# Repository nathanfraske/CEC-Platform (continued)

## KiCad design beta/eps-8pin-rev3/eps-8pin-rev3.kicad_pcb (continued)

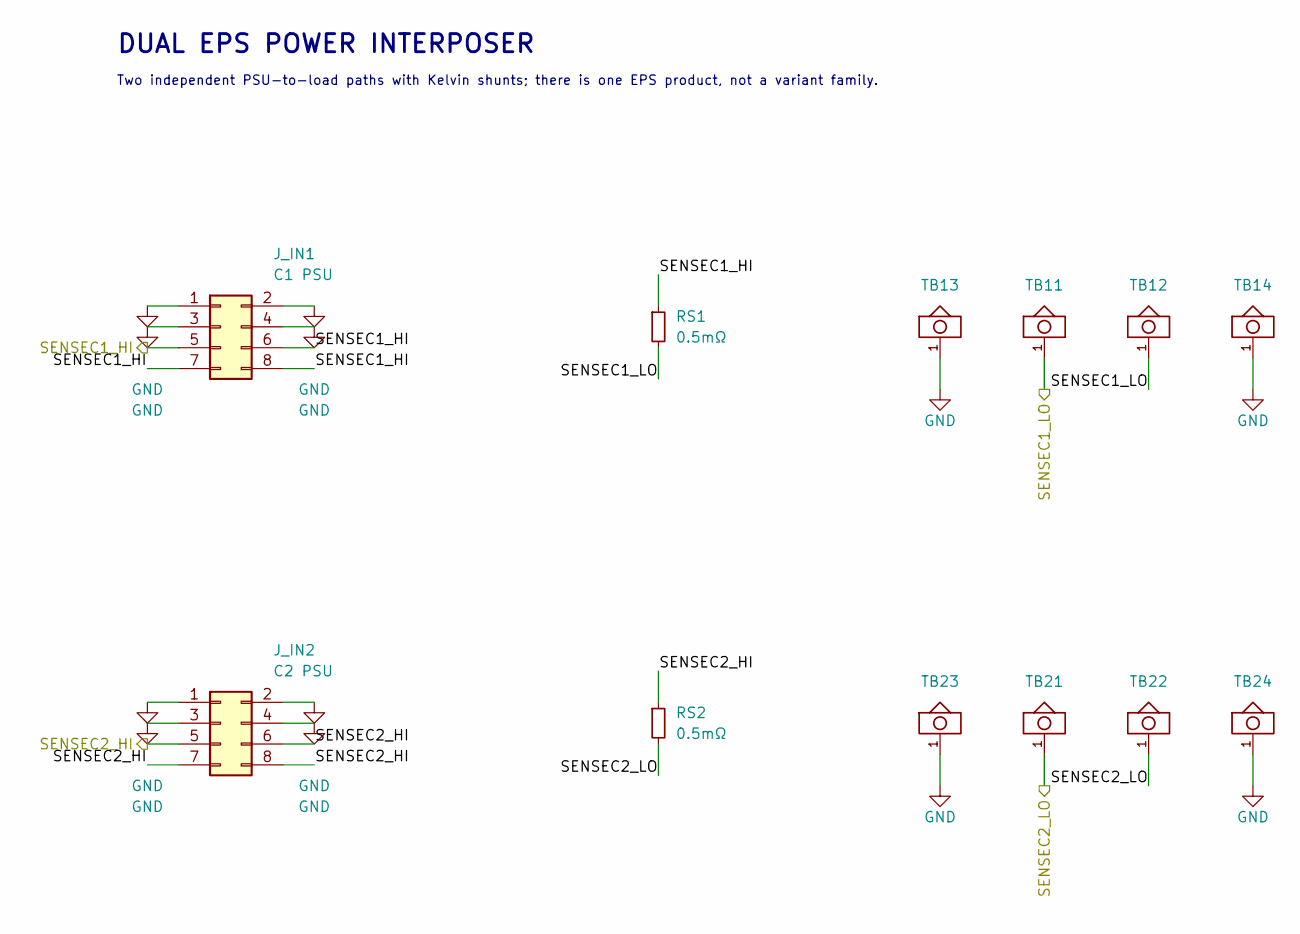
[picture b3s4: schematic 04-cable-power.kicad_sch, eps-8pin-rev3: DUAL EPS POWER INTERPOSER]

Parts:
J_IN1: C1 PSU; Molex_Mini-Fit_Jr_87427-0802_2x04_P4.20mm_RA; MPN 87427-0802
J_IN2: C2 PSU; Molex_Mini-Fit_Jr_87427-0802_2x04_P4.20mm_RA; MPN 87427-0802
RS1, RS2: 0.5mΩ; R_2512_6332Metric; MPN CSS2H-2512R-L500F
TB11, TB12, TB13, TB14, TB21, TB22, TB23, TB24: XFCN T34069; XFCN_T34069_THT_M3_40A; Current Rating 40 A manufacturer-stated; qualification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; MPN T34069; LCSC C481452

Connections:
/SENSEC1_HI: J_IN1.5, J_IN1.6, J_IN1.7, J_IN1.8, RS1.1; also elsewhere on the board
/SENSEC1_LO: RS1.2, TB11.1, TB12.1; also elsewhere on the board
/SENSEC2_HI: J_IN2.5, J_IN2.6, J_IN2.7, J_IN2.8, RS2.1; also elsewhere on the board
/SENSEC2_LO: RS2.2, TB21.1, TB22.1; also elsewhere on the board

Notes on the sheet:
DUAL EPS POWER INTERPOSER
Two independent PSU-to-load paths with Kelvin shunts; there is one EPS product, not a variant family.

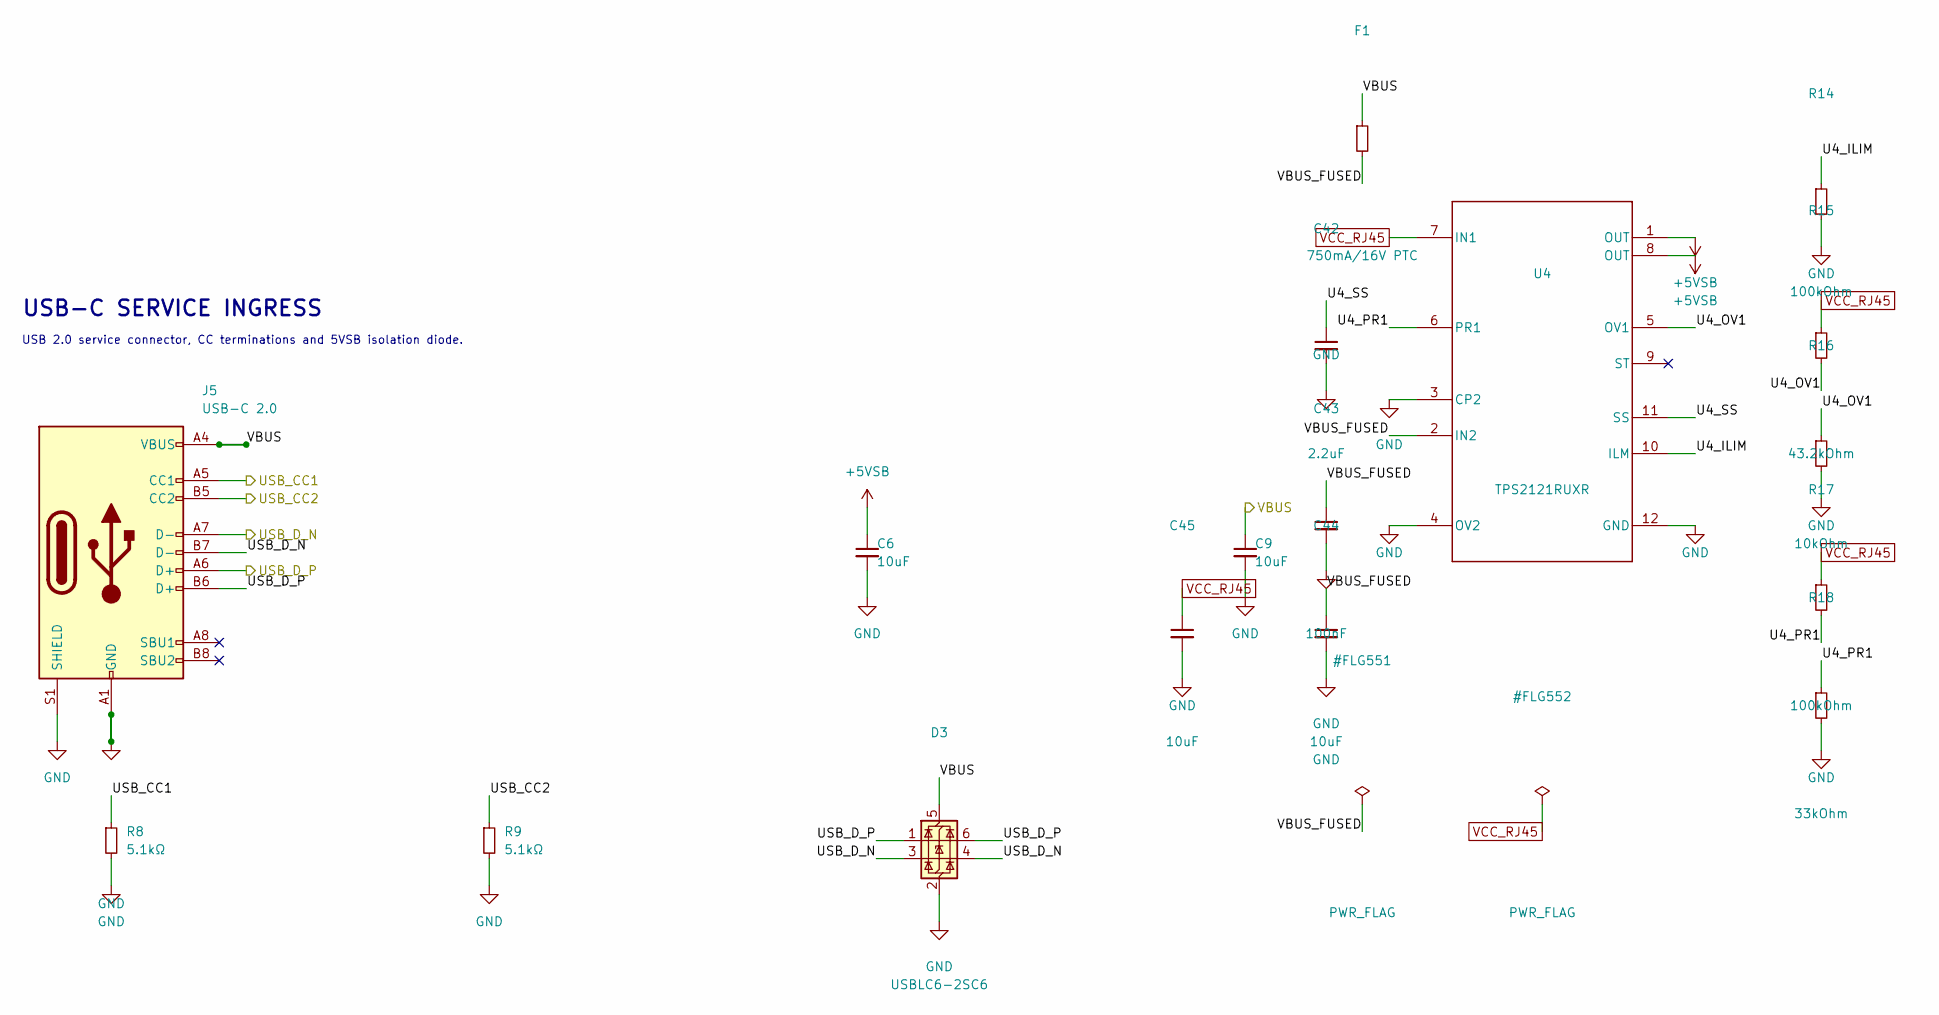
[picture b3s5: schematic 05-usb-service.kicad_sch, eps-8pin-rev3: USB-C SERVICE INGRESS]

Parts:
C6, C9, C44, C45: 10uF; C_0805_2012Metric; MPN CL21A106KAYNNNE; LCSC C15850
C42: 2.2uF; C_0603_1608Metric; MPN CL10A225KO8NNNC; LCSC C23630
C43: 100nF; C_0402_1005Metric; MPN CL05B104KO5NNNC; LCSC C1525
D3: USBLC6-2SC6; SOT-23-6; MPN USBLC6-2SC6; LCSC C2687116
F1: 750mA/16V PTC; R_1206_3216Metric; MPN 1206L075/16WR; LCSC C371166
J5: USB-C 2.0; USB_C_Receptacle_GCT_USB4215-03-A; MPN USB4215-03-A; LCSC C37616412
R8, R9: 5.1kΩ; R_0402_1005Metric; MPN 0402WGF5101TCE; LCSC C25905
R14, R17: 100kOhm; R_0402_1005Metric; MPN 0402WGF1003TCE; LCSC C25741
R15: 43.2kOhm; R_0402_1005Metric; MPN 0402WGF4322TCE; LCSC C25894
R16: 10kOhm; R_0402_1005Metric; MPN 0402WGF1002TCE; LCSC C25744
R18: 33kOhm; R_0402_1005Metric; MPN 0402WGF3302TCE; LCSC C25779
U4: TPS2121RUXR; RUX0012A; MPN TPS2121RUXR; LCSC C485916

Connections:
/USB-C SERVICE INGRESS/U4_ILIM: R14.1, U4.10 (ILM)
/USB-C SERVICE INGRESS/U4_OV1: R15.2, R16.1, U4.5 (OV1)
/USB-C SERVICE INGRESS/U4_PR1: R17.2, R18.1, U4.6 (PR1)
/USB-C SERVICE INGRESS/U4_SS: C42.1, U4.11 (SS)
/USB-C SERVICE INGRESS/VBUS_FUSED: C43.1, C44.1, F1.2, U4.2 (IN2)
/USB_CC1: J5.A5 (CC1), R8.1
/USB_CC2: J5.B5 (CC2), R9.1
/USB_D_N: D3.3 (I/O2), D3.4 (I/O2), J5.A7 (D-), J5.B7 (D-); also elsewhere on the board
/USB_D_P: D3.1 (I/O1), D3.6 (I/O1), J5.A6 (D+), J5.B6 (D+); also elsewhere on the board
/VBUS: C9.1, D3.5 (VBUS), F1.1, J5.A4 (VBUS), J5.A9 (VBUS), J5.B4 (VBUS), J5.B9 (VBUS)
VCC_RJ45: C45.1, R15.1, R17.1, U4.7 (IN1); also elsewhere on the board

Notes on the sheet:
USB-C SERVICE INGRESS
USB 2.0 service connector, CC terminations and 5VSB isolation diode.

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
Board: 4 copper layers, 66 parts (0 on the bottom side), 35 nets, no tracks yet.

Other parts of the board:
H1, H2, H3: MountingHole_3.2mm_M3_Pad_Via

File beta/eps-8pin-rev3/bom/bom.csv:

Reference,Qty,Value,Footprint,MPN,Manufacturer,LCSC,LC_Stock,Chosen_Distributor,Datasheet,Validated,DNP,Notes
"C1,C2",2,1uF,C_0603_1608Metric,CL10A105KB8NNNC,Samsung,C15849,,,,,,
"C3,C4,C5,C8,C10,C11,C20,C21,C30,C31,C40,C43",12,100nF,C_0402_1005Metric,CL05B104KO5NNNC,Samsung,C1525,,,https://product.samsungsem.com/mlcc/CL05B104KO5NNN.do,,,U4 IN2 local high-frequency bypass; place at IN2 and GND.
C42,1,2.2uF,C_0603_1608Metric,CL10A225KO8NNNC,Samsung,C23630,,,https://product.samsungsem.com/mlcc/CL10A225KO8NNN.do,,,U4 soft-start capacitor.
"C6,C9,C44,C45",4,10uF,C_0805_2012Metric,CL21A106KAYNNNE,Samsung,C15850,,,https://product.samsungsem.com/mlcc/CL21A106KAYNNN.do,,,"U4 IN1 local bypass; place at IN1 and GND.,U4 IN2 local bulk bypass; place at IN2 and GND."
C7,1,4.7uF,C_0805_2012Metric,CL21A475KAQNNNE,Samsung,C1779,,,https://product.samsungsem.com/mlcc/CL21A475KAQNNN.do,,,"LP5907 +3V3 bulk selected so the complete output node is 6.5uF nominal, within the 10uF application range and below the 11.1uF input node."
D1,1,PESD5V0S1BA,D_SOD-323,PESD5V0S1BA,HXY MOSFET,C5261083,,,https://www.lcsc.com/datasheet/C5261083.pdf,,,
D3,1,USBLC6-2SC6,SOT-23-6,USBLC6-2SC6,UMW,C2687116,,,https://datasheet.lcsc.com/lcsc/2206231215_UMW-Youtai-Semico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,,,Low-capacitance USB D+/D- ESD array with VBUS reference.
F1,1,750mA/16V PTC,R_1206_3216Metric,1206L075/16WR,Littelfuse,C371166,,,https://www.lcsc.com/datasheet/C371166.pdf,,,"750mA hold, 1.5A trip, 16V resettable PTC on USB VBUS ingress."
J1,1,TO-HUB,RJ45_FTP_Shielded_Horizontal,KH-RJ45-58-8P8C,Kinghelm,C2683360,,,https://www.lcsc.com/datasheet/C2683360.pdf,,,
J5,1,USB-C 2.0,USB_C_Receptacle_XKB_U262-16XN-4BVC11,U262-161N-4BVC11,XKB Connection,C319148,,,https://datasheet.lcsc.com/szlcsc/1811141824_XKB-Enterprise-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,,,
J_IN1,1,C1 PSU,Molex_Mini-Fit_Jr_87427-0802_2x04_P4.20mm_RA,87427-0802,Molex,,,,https://www.molex.com/content/dam/molex/molex-dot-com/produc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,,,
J_IN2,1,C2 PSU,Molex_Mini-Fit_Jr_87427-0802_2x04_P4.20mm_RA,87427-0802,Molex,,,,https://www.molex.com/content/dam/molex/molex-dot-com/produc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,,,
"R1,R3,R4",3,2.2kΩ,R_0402_1005Metric,0402WGF2201TCE,UNI-ROYAL,C25879,,,,,,
"R14,R17",2,100kOhm,R_0402_1005Metric,0402WGF1003TCE,UNI-ROYAL,C25741,,,https://www.lcsc.com/product-detail/C25741.html,,,"U4 ILIM = 100k, approximately 1.24A typical.,U4 PR1 divider top."
R15,1,43.2kOhm,R_0402_1005Metric,0402WGF4322TCE,UNI-ROYAL,C25894,,,https://www.lcsc.com/product-detail/C25894.html,,,U4 OV1 top; 43.2k/10k gives 5.639V nominal and 5.287..5.948V at specified extremes.
R16,1,10kOhm,R_0402_1005Metric,0402WGF1002TCE,UNI-ROYAL,C25744,,,https://www.lcsc.com/product-detail/C25744.html,,,U4 OV1 divider bottom.
R18,1,33kOhm,R_0402_1005Metric,0402WGF3302TCE,UNI-ROYAL,C25779,,,https://www.lcsc.com/product-detail/C25779.html,,,U4 PR1 divider bottom; approximately 4.27V validity threshold.
"R2,R10,R19",3,10kΩ,R_0402_1005Metric,0402WGF1002TCE,UNI-ROYAL,C25744,,,https://www.lcsc.com/product-detail/C25744.html,,,10 kohm follows Espressif ESP32-C6-DevKitC-1; GPIO8 must be high with GPIO9 low for joint download boot
R7,1,100kΩ,R_0402_1005Metric,0402WGF1003TCE,UNI-ROYAL,C25741,,,,,,
"R8,R9",2,5.1kΩ,R_0402_1005Metric,0402WGF5101TCE,UNI-ROYAL,C25905,,,,,,
"RS1,RS2",2,0.5mΩ,R_2512_6332Metric,CSS2H-2512R-L500F,Bourns,,,,https://www.bourns.com/docs/product-datasheets/css2h-2512.pdf,,,"OQ-11 locked selection on the single current EPS product: 0.5mOhm, CSS2H-2512R-L500F. Distributor availability remains a BOM-freeze check."
SW1,1,BOOT,TS-1088-AR02016,TS-1088-AR02016,XUNPU,C720477,,,https://www.lcsc.com/datasheet/C720477.pdf,,,
SW2,1,RESET,TS-1088-AR02016,TS-1088-AR02016,XUNPU,C720477,,,https://www.lcsc.com/datasheet/C720477.pdf,,,
"TB11,TB12,TB13,TB14,TB21,TB22,TB23,TB24",8,XFCN T34069,XFCN_T34069_THT_M3_40A,T34069,XFCN,C481452,,,https://www.lcsc.com/datasheet/C481452.pdf,,,"XFCN side-clamp PCB soldering terminal; M3; four THT legs, all one electrical node. Manufacturer states 40 A and 0.5 N*m thread torque. JLC Extended, THT manual/wave assembly. PCB hole pattern and clamp datum remain incoming-sample gates."
U1,1,ESP32-C6-MINI-1-N4,ESP32-C6-MINI-1,ESP32-C6-MINI-1-N4,Espressif Systems,C5736265,,,https://documentation.espressif.com/esp32-c6-mini-1_mini-1u_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,,,
"U10,U11",2,INA238,VSSOP-10_3x3mm_P0.5mm,INA238AIDGSR,Texas Instruments,C2868250,,,https://www.ti.com/lit/ds/symlink/ina238.pdf,,,
U2,1,TJA1051T/3,SOIC-8_3.9x4.9mm_P1.27mm,TJA1051T/3/1J,NXP Semiconductors,C38695,,,https://www.nxp.com/docs/en/data-sheet/TJA1051.pdf,,,
"U20,U21",2,INA181A2IDBVR,SOT-23-6,INA181A2IDBVR,Texas Instruments,C2058784,,,https://www.ti.com/lit/ds/symlink/ina181.pdf,,,
U3,1,LP5907MFX-3.3,SOT-23-5,LP5907MFX-3.3/NOPB,Texas Instruments,C80670,,,https://www.ti.com/lit/ds/symlink/lp5907.pdf,,,
"U30,U31",2,TLV7011DBVR,SOT-23-5,TLV7011DBVR,Texas Instruments,C702117,,,https://www.ti.com/lit/ds/symlink/tlv7011.pdf,,,
U4,1,TPS2121RUXR,RUX0012A,TPS2121RUXR,Texas Instruments,C485916,,,https://www.ti.com/lit/ds/symlink/tps2121.pdf,,,Protected USB/RJ45 service-power mux; OUT is the board +5VSB rail.

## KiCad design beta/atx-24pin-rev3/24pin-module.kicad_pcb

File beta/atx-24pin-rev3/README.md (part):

# atx-24pin-rev3 — current hierarchical BETA

> **CURRENT OUTPUT INTERFACE (2026-08-12):** the live schematic/PCB replaces
> the blade-era TB field with four XFCN T34069 rail terminals and two
> TTR32100127-0600 GND terminals. `J_SIG1` is now the exact Samtec
> **SSQ-102-03-G-D 2×2 vertical socket**, mating daughterboard
> **TSW-102-16-G-D-RA**. Pin order is 1=`-12V`, 2=`PS_ON#`, 3=`PWR_OK`,
> 4=`GND` using Samtec odd/even-by-column numbering. The older 2×5/1×4 and
> blade descriptions below are retained only as dated design provenance.

> **CURRENT STATUS (2026-08-03):** `24pin-module.kicad_sch` plus its five
> functional leaves is the authoritative source. The direct Hub RJ-45 `J1` is
> removed; the segmented `J6P/J6C/J6D` mezzanine owns the Hub data/detect/stack
> link and `J2` remains the dedicated Hub power connector. The dead-bug
> assembly has the ATX input `J3` on the bottom edge and the output blade/signal
> field on the top edge. The reflected Hub puts its four RJ-45 mouths on the
> assembly right. **2026-09-22 correction:** the mechanical target is now 22 mm;
> the old 18 mm / M2.5 hardware is rejected for over-insertion. ASB-2022E supports
> and SSCF-M2-5-A2 screws are selected, with slim plated M2 lugs in the paired
> seeds. The conditional 3D stack checks pass; physical release remains withheld.
> Use `docs/hub-atx-stack-placement-inputs-20260922.json`, with the evidence in
> `docs/hub-atx-3d-placement-qualification-2026-09-22.md`. Do not treat the
> hardware BOM as an order approval. All earlier flat/synced-copy/"PCB not
> started" prose below is historical provenance, not current build guidance.

> **STATUS (2026-07-04, spec §2.8 v1.4.0 output-architecture revision, owner-ratified):** the
> schematic is now **BETA-2**. J4 (the Mini-Fit Jr 24-circuit MALE output header, previously
> marked WORKING BASIS pending the D-5a ruling) is **DELETED** — it retires the two-male-header
> output form and the female-to-female 24-pin ATX bridging-cable premise that went with it.
> Output rails now cross the ratified **all-Keystone/TE connector-daughterboard interface**
> (`docs/standard-tier-review/output-daughterboard-study-2026-07-04.md` §8.9–§8.10,
> `docs/standard-tier-review/blade-fit-check-2026-07-04.md`): **9 blade-joint receptacles**
> (`TB1`–`TB9` — FINAL PART per iteration 7, 2026-07-06, owner-ratified: **TE 63969-1** FASTON
> .250 PCB receptacle, LCSC C2961150; the Keystone 3586/3557 mentioned below in this
> paragraph's original text were interim picks, retired to vendored fallbacks — the full
> selection chain lives in each TB's Note property + blade-fit-check-2026-07-04.md addendum 7, one per ratified joint — 12V×1,
> 5V×2, 3.3V×1, 5VSB×1, GND×4), each a single-pin part landing on the SAME post-shunt rail
> node its share of J4 used to carry (`TB1`→`/SENSE12V_LO`, `TB2`/`TB3`→`+5V_MAIN`,
> `TB4`→`/SENSE3V3_LO`, `TB5`→`/SENSE5VSB_LO`, `TB6`–`TB9`→`GND`), plus **one 2×5 2.54 mm
> signal header** (`J_SIG`, `cec:CEC_CONN_2x5` on the vendored
> `cec-Connector_PinHeader_2.54mm:PinHeader_2x05_P2.54mm_Vertical` footprint) carrying the
> flat schematic's actual J4 signal set — pin 1 = PS_ON#, pin 2 = PWR_OK, pin 3 = −12V, pin 4 =
> GND (local reference), pins 5–10 reserved/no-connect. The header's signal list was derived
> from the CURRENT flat netlist, not invented: no 5VSB-sense/remote-sense net exists on this
> board's J4 today, so none is populated. **Sense-return contacts are explicitly NOT added** —
> the output-daughterboard study's §5 decision box (e) is still open with the owner. The mating
> daughterboard (TE 63849-1 `.250"` FASTON tabs, LCSC C86469) is a separate, not-yet-created
> deliverable; this board only carries the main-board half of the interface. Netlist-verified
> before/after: every other net on this board (INA228 sense taps, the TPS2121 mux, the LP5907
> LDO, etc.) is byte-for-byte unchanged — only the 8 real rail/signal nets J4 touched gained
> their replacement member(s), plus the trivial per-pin unconnected-net churn from J4's dropped
> NC pin and J_SIG's 6 new reserved pins. `bom/bom.csv` regenerated (`kicad-cli sch export
> bom`); `fp-lib-table` gained `cec-Connector_Blade` and `cec-Connector_PinHeader_2.54mm`.
> ERC/audit-sch introduce zero new errors and zero new finding CLASSES — the only new warnings
> are the same well-documented benign `lib_symbol_mismatch` noise every other power-port
> instance on this board already produces (proportional to the net new GND/+5V_MAIN power-port
> count), and the pre-existing 1 `pin_not_driven` error (U2 CAN TXD) and pre-existing
> `wire_through_body`/`missing_lib_symbol` audit findings are untouched, unrelated to this
> change.
>
> **STATUS (2026-07-03, beta schematic wave, K2 ruling):** the schematic is now **BETA-1**
> (see the title block and `docs/standard-tier-review/beta-splices/atx-24pin.md` for the full
> record). This pass: (1) closed the K1 gate — the J6 mezzanine pin-map contradiction between
> this board's netlist and `docs/mezzanine-stack-design-2026-06-24.md` — in the SCHEMATIC's
> favor (the design doc was corrected; rev3's J6 and `hubs/hub-rev2`'s J_MEZZ already agreed
> with each other, so no re-pin was needed or done); (2) fixed RS4 (the 25 mOhm 5VSB shunt) onto
> a true 4-terminal Kelvin land (`CEC_SHUNT_4T` + the Vishay WSK2512 footprint, matching the
> alpha board's RS6 treatment — was a 2-pad land conflating current path and INA228 sense taps);
> (3) added the H3/H3a standalone-mode suite (USBLC6-2SC6 USB ESD, a VBUS clamp, a populated
> VBUS ferrite bead, a 0R-default port-entry bead on +5V_SYS, and a DNP CAN common-mode-choke
> position with a parallel 0R bypass so CAN stays continuous unpopulated); (4) marked the J4
> ATX output connector's form as **WORKING BASIS** pending the D-5a owner ruling (still the
> placeholder male Mini-Fit Jr header); (5) discovered and fixed a real pre-existing defect: J2
> (the Hub-power JST) was still wired to the stale `+5VSB` input net instead of the mux's
> `+5V_SYS` output, contradicting the respin doc's own stated intent.
>
> **PCB is UNTOUCHED** — still byte-identical to `../atx-24pin-rev2`'s fully-placed/routed
> layout, which predates all of the above (no mux, no mezzanine header, no C6, no H3 suite, no
> Kelvin RS4). Layout starts FRESH from this schematic; the `DRAFT` marker stays in place (CI
> correctly skips PCB-side checks) until that pass happens. Do not run "Update PCB from
> Schematic" expecting a small diff — treat the PCB as needing a full new placement/route pass.
>
> Earlier scaffold history (2026-06-24, respin design + build) is preserved below for
> provenance; the "synced copy, do not edit directly" convention it describes is now STALE —
> this schematic has been hand-spliced far beyond a sync copy and IS the source of truth for
> this board going forward (rev2 stays frozen/ordered, unrelated to this file).

Originated as the same circuit as [`../atx-24pin`](../atx-24pin) (the canonical
24-pin ATX interposer) with a different PCB layout only — 24-pin input (J3)
with a right-angle cable exit. That premise is now STALE for the output side:
this schematic has since diverged (BETA-1/BETA-2 hand-splices) and no longer
carries a 24-pin output header at all — see the BETA-2 status block above.

## Output architecture (§2.8 v1.4.0, BETA-2)

Input (J3, PSU side) is unchanged: a Molex Mini-Fit Jr 24-circuit male header.
Output no longer uses a board-mount male header + bridging cable. Instead the
module's 9 rail/return nodes each land on their own Keystone 3586 SMT
universal-entry blade clip (`TB1`–`TB9`) — the main-board half of the
connector-daughterboard interface. The clips mate with TE 63849-1 `.250"`
FASTON tabs on a passive daughterboard (a separate deliverable, not yet
created in this repo); see `docs/standard-tier-review/output-daughterboard-
study-2026-07-04.md` and `blade-fit-check-2026-07-04.md` for the ratified
joint counts, the fit-check, and the two remaining owner bench gates (gang
mating-force measurement; clip-cluster confirm-soak/thermal-cycle contact-R
trend) before first fab. The low-current ATX standards circuits (PS_ON#,
PWR_OK, −12V) ride a separate 2×5 2.54 mm signal header (`J_SIG`) instead of
a blade clip; see the BETA-2 status block for its exact pin map.

## Historical rev2-only issue — RJ-45 VCC paralleled the JST feed

rev2 ties **J1 pin 1 (RJ-45 VCC)** to `+5VSB`, so the module feeds the Hub on
**both** the dedicated JST 5VSB feed **and** its RJ-45 VCC pin, in parallel.
Because the Hub power mux sits only in the JST leg (JST = mux input, RJ-45 VCC =
mux output), a **short RJ-45 patch** makes the RJ-45 the lower-resistance path —
it carries the majority of the bulk current (up to ~1.7 A at 3 A total, over the
**1.5 A RJ-45 contact rating**) and bypasses the mux's PSU/USB OR-ing. Rev3 first
left J1.1 open and now removes J1 entirely; rev2 is ordered as-is, so mitigate at
bring-up — any one of:

1. **Long RJ-45 patch (≥1.5–2 m)** on the 24-pin↔Hub link: the conductor
   resistance then exceeds the JST+mux path, so the JST carries the bulk. No mod.
2. **Keep total 5VSB low:** cap the firmware LED budget and don't run all ports
   full-white. Under ~2 A total, even a 50/50 split keeps the RJ-45 VCC well
   under 1.5 A.
3. **Bodge — open J1 pin 1:** lift the RJ-45 VCC pin or knife-cut its trace to
   `+5VSB`, emulating the rev3 fix. Most robust; do this if you'll push full
   load. The module still self-powers from its ATX tap.

**Decision (prototype run):** go with mitigation 2 — keep the **OQ-2 firmware
5VSB cap conservative** (target ~2 A total for the rev2 prototype) so the RJ-45
VCC stays under 1.5 A regardless of patch length. No rev2 bodge and no Hub-side
workaround; the real fix is **24-pin rev3** (J1.1 no-connect). Rule of thumb:
don't run a fully-populated, full-LED system on an un-bodged rev2.

## Archived scaffold convention (superseded)
The schematic here is a **synced copy**. The source of truth is
`../atx-24pin/24pin-module.kicad_sch`.

1. Edit the schematic in `../atx-24pin`.
2. Run `./sync-schematic.sh` here to refresh this copy.
3. **Tools → Update PCB from Schematic** in this project's board.

Do not edit this copy directly — `sync-schematic.sh` overwrites it from canonical.

## PCB
Starts as a blank slate: **only J3 and J4 are placed**, on the inherited 1 oz
stackup + netclasses (USB/CAN/Power/HighCurrent) + design rules. Everything else
arrives via *Update PCB from Schematic*, ready to place around the right-angle
header arrangement. (A fresh DRC will show unconnected items until that import.)

---

## 2026-07-14 — ATX control-signal interaction block (owner-approved + landed)

Owner-approved same-day (study: `docs/standard-tier-review/atx24-sense-wire-interaction-study-2026-07-14.md`,
ruling recorded in its Status block + `docs/owner-queue.md`). Spliced by `scripts/splice_24pin_atxctl.py`
(idempotent-guarded); ERC delta = +7 documented-benign Unspecified-pin warnings only (the 1 pre-existing
U2 TXD `pin_not_driven` error is unchanged); netlist diff verified node-for-node (69 untouched nets
byte-identical, 8 new nets); `bom/bom.csv` regenerated (also trued up the stale `J_SIG1` 2x5 row to the
as-built 1x4).

What it adds (all hanging on the existing `/ATX_PWROK` / `/ATX_PSON` / `/ATX_NEG12V` pass-through nets —
J_SIG1 map and §2.8 output architecture untouched):

- **PWR_OK read** (restores the alpha/netmap-§4 pattern rev3 had regressed): R70 1k → U4 74LVC1G17
  (5V-tolerant Schmitt @3V3, C62) → `/PWROK_SENSE` → **IO4**. Interrupt-timestamps the ATX 100–500 ms
  T_pwr_ok window.
- **PS_ON# read**: R71 1k → U8 74LVC1G17 (high-Z — does not load the PSU's internal pull-up, C63) →
  `/PSON_SENSE` → **IO5**. Lets firmware distinguish motherboard-asserting from CEC-asserting and verify
  line integrity after own assert.
- **PS_ON# open-drain drive (NEW capability)**: **IO3** → R72 100Ω → gate (R73 100k pull-down =
  RELEASED at reset/brownout/crash, safety-critical, never DNP) → Q1 AO3400A drain → `/ATX_PSON`,
  source → GND. Wired-OR with the motherboard: can force PSU ON, can never source or force off.
- **−12V measurement (NEW)**: divider hung **+3V3↔−12V** (R74 15k / R75 100k → node ≈1.30 V @ −12.0 V,
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
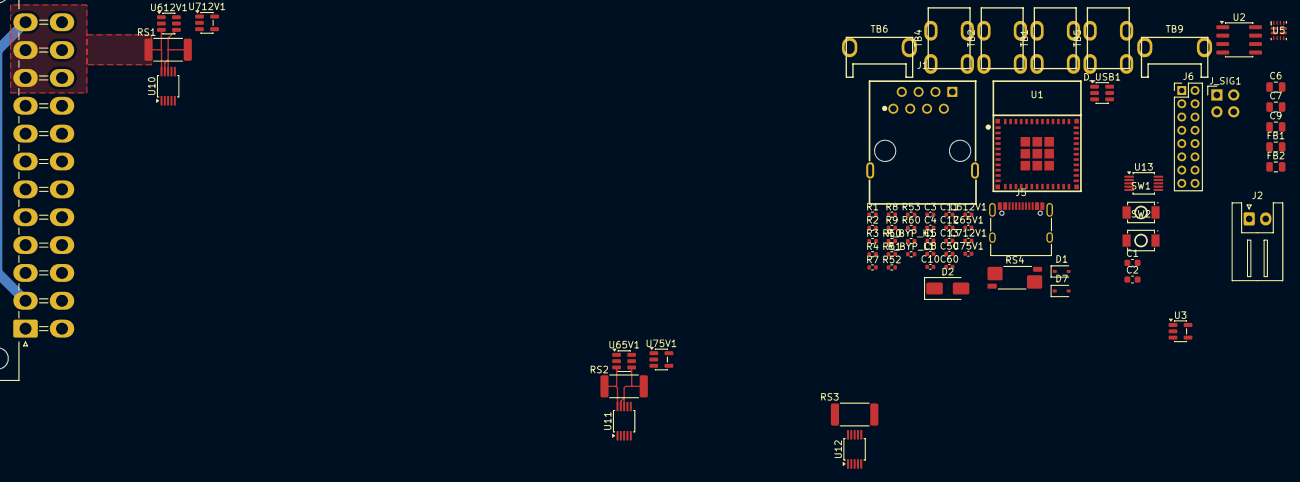
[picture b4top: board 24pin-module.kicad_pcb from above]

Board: 4 copper layers, 69 parts (0 on the bottom side), 44 nets.

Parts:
C1, C2: 1uF; C_0603_1608Metric
C3, C4, C5, C8, C10, C11, C12, C13, C60, C65V1, C75V1, C612V1, C712V1: 100nF; C_0402_1005Metric
C6, C7, C9: 10uF; C_0805_2012Metric
C50: 2u2; C_0402_1005Metric
D1, D7: PESD5V0S1BA; D_SOD-323
D2: SS34; D_SMA
D_USB1: USBLC6-2SC6; SOT-23-6
FB1: 600R@100MHz FB (MPZ2012S601AT000); C_0805_2012Metric
FB2: 0R (FB position, populate on EMC evidence); C_0805_2012Metric
J1: TO-HUB; RJ45_FTP_Shielded_Horizontal
J2: TO-HUB-PWR; JST_XH_S2B-XH-A_1x02_P2.50mm_Horizontal
J3: ATX-24 PSU; Molex_Mini-Fit_Jr_5569-24A1_2x12_P4.20mm_Horizontal
J5: USB-C 2.0; USB_C_Receptacle_XKB_U262-16XN-4BVC11
J6: TO-HUB-STACK; PinHeader_2x08_P2.00mm_Vertical
J_SIG1: SSQ-102-03-G-D; Samtec_SSQ-102-03-G-D_2x02_P2.54mm_Vertical
R1, R3, R4: 2.2kΩ; R_0402_1005Metric
R2, R51, R60: 10kΩ; R_0402_1005Metric
R7, R52: 100kΩ; R_0402_1005Metric
R8, R9: 5.1kΩ; R_0402_1005Metric
R50: 20kΩ; R_0402_1005Metric
R53: 33kΩ; R_0402_1005Metric
RS1, RS2, RS3: 2mΩ; R_2512_6332Metric
RS4: 25mΩ; R_Shunt_Vishay_WSK2512_6332Metric_T1.19mm
R_BYP_H1: 0Ω; R_0402_1005Metric
R_BYP_L1: 0Ω; R_0402_1005Metric
SW1: BOOT; TS-1088-AR02016
SW2: RESET; TS-1088-AR02016
TB1, TB2, TB4, TB5: XFCN T34069; XFCN_T34069_THT_M3_40A
TB6, TB9: TTR32100127-0600; XFCN_TTR32100127-0600_THT_M3_60A
U1: ESP32-C6-MINI-1-N4; ESP32-C6-MINI-1
U2: TJA1051T/3; SOIC-8_3.9x4.9mm_P1.27mm
U3: LP5907MFX-3.3; SOT-23-5
U5: TPS2121RUXR; RUX0012A
U10, U11, U12, U13: INA238; VSSOP-10_3x3mm_P0.5mm
U65V1, U612V1: INA181A2IDBVR; SOT-23-6
U75V1, U712V1: TLV7011DBVR; SOT-23-5

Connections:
+3V3: C2.1, C3.1, C7.1, C8.1, C10.1, C11.1, C12.1, C13.1, C65V1.1, C75V1.1, C612V1.1, C712V1.1, R2.1, R4.2, R51.2, U1.3 (3V3), U2.5 (VIO), U3.5 (OUT), U11.2 (A0), U12.1 (A1), U13.1 (A1), U13.2 (A0), U13.6 (VS), U65V1.6 (VS), U75V1.5 (VCC), U612V1.6 (VS), U712V1.5 (VCC)
+5VSB: J3.9 (+5VSB), RS4.1 (I1), U5.2 (IN2)
+5V_MAIN: R52.1, RS2.2, TB2.1, U5.7 (IN1), U11.8 (Vbus), U11.9 (Vin-), U65V1.4 (IN-)
+5V_SYS: C1.1, C4.1, C6.1, D2.1 (K), FB2.1, U2.3 (VCC), U3.1 (IN), U3.3 (EN), U5.1 (OUT), U5.8 (OUT)
/+5V_SYS_PORT: FB2.2, J2.1 (VCC), J6.1 (+5V_SYS), J6.2 (+5V_SYS), J6.3 (+5V_SYS)
/CAN_H: R_BYP_H1.2, U2.7 (CANH)
/CAN_H_BUS: J1.3 (CAN1_H), J6.5 (CAN_H), R_BYP_H1.1
/CAN_L: R_BYP_L1.2, U2.6 (CANL)
/CAN_L_BUS: J1.6 (CAN1_L), J6.6 (CAN_L), R_BYP_L1.1
/CAN_RX: U1.27 (IO21), U2.4 (RXD)
/CAN_TX: U1.26 (IO20), U2.1 (TXD)
/DET5V: U1.29 (IO23), U75V1.1 (OUT)
/DET12V: U1.28 (IO22), U712V1.1 (OUT)
/DETAMP5V: U65V1.1 (OUT), U75V1.3 (IN+)
/DETAMP12V: U612V1.1 (OUT), U712V1.3 (IN+)
/DETECT: D1.1 (K), J1.8 (DETECT), J6.11 (DETECT), R1.1, R7.2
/DETECT_SENSE: R7.1, U1.12 (IO0)
/EN: C5.1, R2.2, SW2.2, U1.8 (EN)
/GPIO0: SW1.2, U1.23 (IO9)
/I2C_SCL: R4.1, U1.25 (IO19), U10.5 (SCL), U11.5 (SCL), U12.5 (SCL), U13.5 (SCL)
/I2C_SDA: R3.1 (~_1), U1.24 (IO18), U10.4 (SDA), U11.4 (SDA), U12.4 (SDA), U13.4 (SDA)
/ILIM: R50.1, U5.10 (ILM)
/MUX_ST: R51.1, U5.9 (ST)
/SENSE3V3_HI: J3.1 (+3.3V), J3.2 (+3.3V), J3.12 (+3.3V), J3.13 (+3.3V), RS3.1, U12.10 (Vin+)
/SENSE3V3_LO: RS3.2, TB4.1, U12.8 (Vbus), U12.9 (Vin-)
/SENSE5VSB_HI: RS4.2 (S1), U13.10 (Vin+)
/SENSE5VSB_LO: RS4.4 (I2), TB5.1, U13.8 (Vbus)
/SENSE5VSB_LO_KELVIN: RS4.3 (S2), U13.9 (Vin-)
/SENSE5V_HI: J3.4 (+5V), J3.6 (+5V), J3.21 (+5V), J3.22 (+5V), J3.23 (+5V), RS2.1, U11.10 (Vin+), U65V1.3 (IN+)
/SENSE12V_HI: J3.10 (+12V), J3.11 (+12V), RS1.1, U10.10 (Vin+), U612V1.3 (IN+)
/SENSE12V_LO: RS1.2, TB1.1, U10.8 (Vbus), U10.9 (Vin-), U612V1.4 (IN-)
/SS: C50.1, U5.11 (SS)
/THRESH: C60.1, R60.2, U75V1.4 (IN), U712V1.4 (IN)
/THRESH_PWM: R60.1, U1.19 (IO14)
/USB_CC1: J5.A5 (CC1), R8.1
/USB_CC2: J5.B5 (CC2), R9.1
/USB_DM: D_USB1.3 (I/O2), D_USB1.4 (I/O2), J5.A7 (D-), J5.B7 (D-), U1.17 (IO12)
/USB_DP: D_USB1.1 (I/O1), D_USB1.6 (I/O1), J5.A6 (D+), J5.B6 (D+), U1.18 (IO13)
/VBUS: C9.1, D2.2 (A), FB1.2
/VBUS_RAW: D7.1 (K), D_USB1.5 (VBUS), FB1.1, J5.A4 (VBUS), J5.A9 (VBUS), J5.B4 (VBUS), J5.B9 (VBUS)
GND: C1.2, C2.2, C3.2, C4.2, C5.2, C6.2, C7.2, C8.2, C9.2, C10.2, C11.2, C12.2, C13.2, C50.2, C60.2, C65V1.2, C75V1.2, C612V1.2, C712V1.2, D1.2 (A), D7.2 (A), D_USB1.2 (GND), J1.2 (GND), J1.SH1, J1.SH2, J2.2 (GND), J3.3 (GND), J3.5 (GND), J3.7 (GND), J3.15 (GND), J3.17 (GND), J3.18 (GND), J3.19 (GND), J3.24 (GND), J5.A1 (GND), J5.A12 (GND), J5.B1 (GND), J5.B12 (GND), J5.S1 (SHIELD), J6.4 (GND), J6.7 (GND), J6.10 (GND), J6.12 (GND), J6.14 (GND), J6.15 (GND), J6.16 (GND), J_SIG1.4, R1.2, R8.2, R9.2, R50.2, R53.2, SW1.1, SW2.1, TB6.1, TB9.1, U1.1 (GND), U1.2 (GND), U1.11 (GND), U1.14 (GND), U1.36 (GND), U1.37 (GND), U1.38 (GND), U1.39 (GND), U1.40 (GND), U1.41 (GND), U1.42 (GND), U1.43 (GND), U1.44 (GND), U1.45 (GND), U1.46 (GND), U1.47 (GND), U1.48 (GND), U1.49 (GND), U1.50 (GND), U1.51 (GND), U1.52 (GND), U1.53 (GND), U2.2 (GND), U2.8 (S), U3.2 (GND), U5.3 (CP2), U5.4 (OV2), U5.5 (OV1), U5.12 (GND), U10.1 (A1), U10.2 (A0), U11.1 (A1), U12.2 (A0), U12.7 (GND), U13.7 (GND), U65V1.2 (GND), U65V1.5 (REF), U75V1.2 (VEE), U612V1.2 (GND), U612V1.5 (REF), U712V1.2 (VEE)
unnamed: R52.2, R53.1, U5.6 (PR1)
unnamed: U10.7 (GND), U11.6 (VS)
unnamed: U11.7 (GND), U12.6 (VS)

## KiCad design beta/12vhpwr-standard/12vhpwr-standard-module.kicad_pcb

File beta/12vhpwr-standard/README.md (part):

# 12VHPWR Standard module

## Current-source warning (2026-09-06)

The current design authority is the hierarchical
`12vhpwr-standard-module.kicad_sch` and its numbered child sheets, selected by
`scripts/cec_beta_manifest.py`. The root PCB is a **stale staging layout**, and
`candidate/candidate.json` also declares its older routed reference stale.
Neither is a current schematic/netlist authority. The canonical replacement
pipeline now synchronizes a separate working copy from the live hierarchy
before intake and placement; it does not overwrite either historical PCB.

The present schematic uses **U16 TLV75533PDRVR**, U5 TPS2121 and six INA240
channels. FL1 remains DNP, with its manufacturer land and explicit CEC-to-TDK
pin mapping assigned. Initial September 6 placements are diagnostic only, not
routed or fabrication-approved boards. See
`../../docs/hub-and-12vhpwr-placement-slices-2026-09-06.md` for provenance,
measured results and remaining work.

## Fan header population (2026-09-07)

J2 is **populated**, not DNP, per the current owner request. It was already in
the hierarchy and PCB geometry; the historical DNP assembly flag was the
discrepancy. The source and both BOMs now agree on JST B3B-PH-K-S(LF)(SN),
LCSC C131339. Its pinout remains switched return / pre-shunt 12 V / tach.
No fan model, mounting standoff or cooling performance is qualified by fitting
the header. See `../../docs/current-beta-fan-header-contact-search-2026-09-07.md`
for fresh remote-source verification and the latest placement results.

## Latest supply-search / group-ranking diagnostic — not promoted (2026-09-09)

A fresh source-synchronized 58 × 72 mm run now constructs and commits **16/16
local supply/return cells**, without the former all-cell rollback. Two generic
repairs make this possible: rejecting an overlong bridge advances its search,
and native-feasible whole supply groups outrank geometrically cheaper blocked
groups. No named-part repair or fabrication-rule relaxation is used.

The local connections reduce opens **222 → 170**, with structural DRC unchanged
at 41. Placement decoupling findings improve **12 → 11**. The saved cell audit
still accepts only 14/16 because two ground-pin distances exceed the unchanged
limit; nine additional proximity findings remain in placement review. **This is
local routing only, not a routed/fab-ready board.** The outline, MCU/interface
positions, mounting holes and wide-power widths are preserved.

See `../../docs/generic-supply-search-ranking-2026-09-09.md` and
`../../build/12vhpwr-supply-escape-fresh-20260909/closeout.json` for exact evidence
and visibly labelled no-body renders. The fresh single-outline stage took
261.9 seconds; 808 tests passed, and the immutable PCIe score/blockers remain
unchanged. Next is complete-loop proximity optimization under the same native
and power-preservation gates, not another blind routing wave.

## Prior ground-access / power-copper diagnostic — not promoted (2026-09-07)

The generic copper constructor now reserves qualified future ground-via sites
and detours only its own power tracks at unchanged width. The fixed-seat replay
improves qualified local-cell proposals **7/16 → 13/16** at 68/72/76 mm and
**7/16 → 12/16** at 80 mm. A separate admission fix prevents rejected narrow
ground links from being counted as successful; both baselines use that fix.

Footprint positions, current hierarchical identity, all six power lanes, wide
track widths, native terminal connectivity and structural DRC locations are
unchanged. **The full cell transaction still rolls back; these are not routed
or fab-admitted boards.** Three local cells remain blocked on the 72 mm review
diagnostic. Changed power paths also need fresh thermal qualification.

See `../../docs/generic-ground-portal-copper-slices-2026-09-07.md` and
`../../build/12vhpwr-ground-portal-final-20260907/closeout.json` for before/after
measurements and exact renders. This was a bounded constructor replay, not a
new full placement wave. The next repair is package-level supply/ground escape
qualification of the complete IC/cap group before placement commitment.

## Prior power-aware orientation diagnostic — not promoted (2026-09-07)

Late orientation proposals now need native proof that required authored copper
can still be constructed. The bounded generic transaction rejects only unsafe
changes and retains passing rotations; it contains no named-part repair.
The fresh four-size cohort retains complete wide-power inventory on **4/4**
candidates, up from **2/4**. The formerly failing 72/76 mm candidates recover
their sixth power lane automatically, with every component centre unchanged.

All four preserve six sensing cells / 444 locked segments, current source
identity, mandatory mounts and lower-right I/O. All 16 supply distances remain
unchanged. **Twelve decoupling findings still remain; no candidate is routing-
or fabrication-admitted.** The 58 x 72 mm diagnostic is shown for review, not
promoted over the canonical board. The 68 mm candidate remains available.

See `../../docs/generic-power-aware-orientation-2026-09-07.md` and
`../../build/12vhpwr-power-aware-full-placement-20260907/power-aware-closeout.json`.
The placement stage took 840.0 seconds; this correctness slice adds about 6.4%
over the previous run, not a speed improvement. PCIe control score/blockers and
all protected source/archive hashes remain unchanged. The next causal repair
is coordinated ground-via access and power-copper planning.

## Prior critical-supply pre-lock diagnostic — not promoted (2026-09-07)

The critical placer now reserves a selected IC with its entire required supply
group before locking. On the same 58 x 68 mm outline, the CAN supply distances
improve from 5.17/6.65 mm to 1.80/1.84 mm; LDO gains and the complete wide-power
inventory are retained. Native construction improves from 5/16 to 8/16 proposals
(seven also meet the source distance limits), but the transaction still rolls
back and aggregate decoupling findings remain 12. This is not routing-admitted.

The 72/76 mm trials expose a required power-lane collision and are excluded.
The generic producer/admission gap is repaired: missing or refused power-lane
construction must now be retained in the sidecar and fail placement admission.
No named-part relocation was used. The 68/80 mm trials preserve that inventory.

See `../../docs/generic-critical-supply-prelock-2026-09-07.md` and
`../../build/12vhpwr-critical-supply-prelock-20260907/critical-supply-closeout.json`.
The four-size stage took 789.4 seconds, about 14% slower than its predecessor;
the old single-cap grid remains a measured runtime bottleneck. Historical
schematic/PCB authority and the PCIe control remain unchanged.

## Prior joint-supply diagnostic — not promoted (2026-09-07)

The generic all-or-nothing multi-supply constructor now places the LDO and
mux with their required capacitors. On the same 58 x 68 mm outline, LDO input
and output distances improve from 9.29/23.08 mm to 1.30/1.30 mm, with native
supply/ground construction possible for both. Six sensing cells / 444 locked
segments and the wide power inventory remain intact.

This is **not a replacement/fab candidate**: the already-fixed CAN group's
capacitors regress, aggregate decoupling findings remain 12, and native
complete-cell construction remains 5/16. The construction transaction rolls
back. Reserve critical devices with their whole supply/ground cell before
locking; do not work around this by moving named caps after placement.

See `../../docs/generic-joint-supply-placement-2026-09-07.md` and
`../../build/12vhpwr-joint-supply-contact-20260907/joint-supply-closeout.json`.
The previous review below remains retained; neither study is routing-admitted.

## Prior supply-group and compaction review (2026-09-07)

Latest bounded cohort:
`build/12vhpwr-supply-copper-guard-compact-20260907`.
The aggressive 58 x 68 mm review is 15% smaller than the retained 58 x 80 mm
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
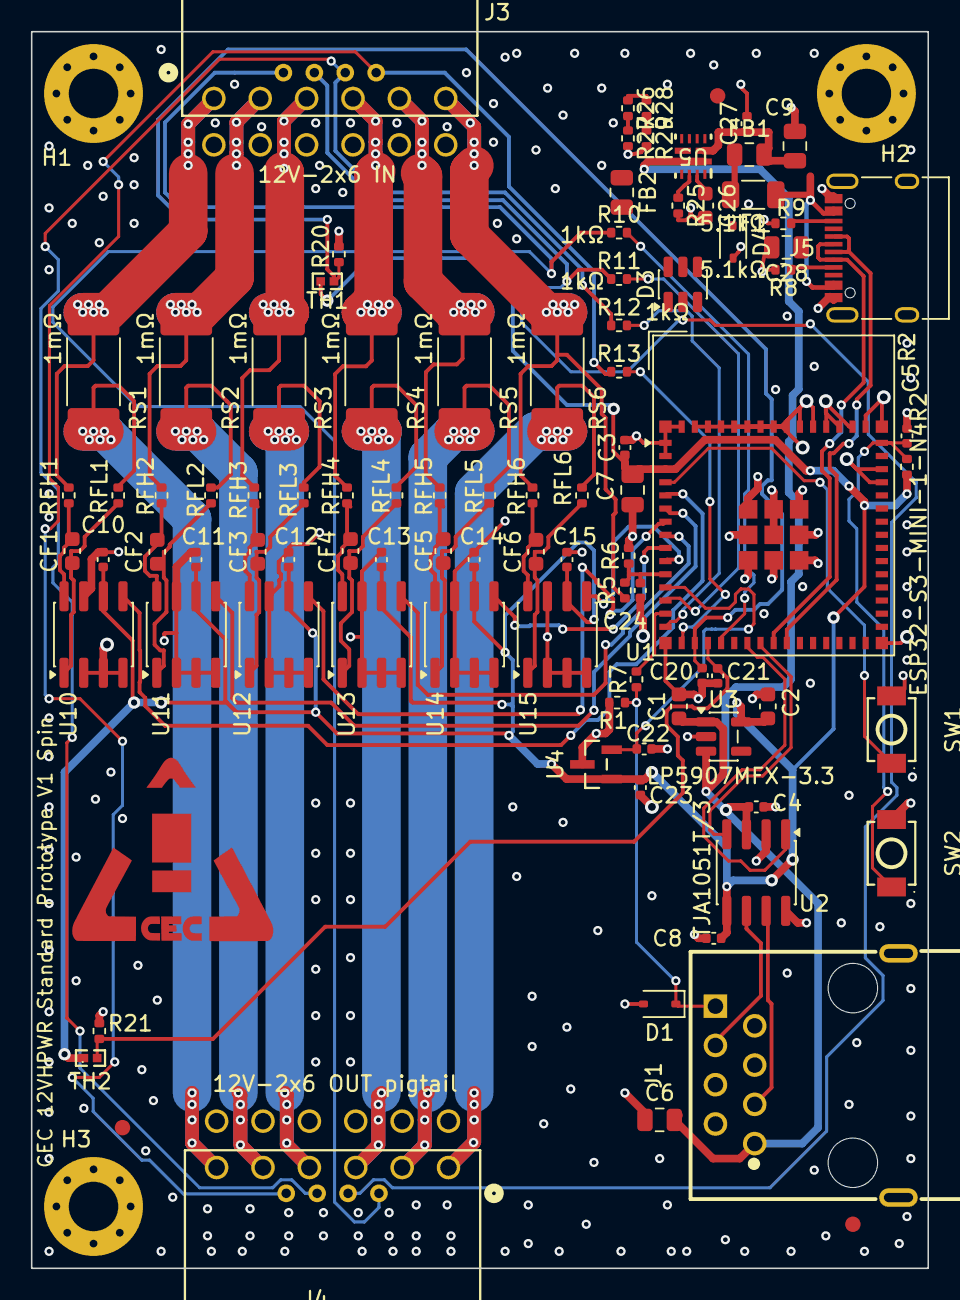
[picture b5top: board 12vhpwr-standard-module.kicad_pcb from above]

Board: 4 copper layers, 58.0 x 80.0 mm, 97 parts (0 on the bottom side), 65 nets.

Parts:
C1, C2: 1uF; C_0603_1608Metric
C3, C4, C5, C8, C10, C11, C12, C13, C14, C15, C20, C21, C22, C23, C27: 100nF; C_0402_1005Metric
C6, C7, C9, C28: 10uF; C_0805_2012Metric
C24: 1nF; C_0402_1005Metric
C26: 2.2uF; C_0603_1608Metric
CF1, CF2, CF3, CF4, CF5, CF6: 470nF; C_0603_1608Metric
D1, D4: PESD5V0S1BA; D_SOD-323
D3: USBLC6-2SC6; SOT-23-6
F1: 750mA/16V PTC; R_1206_3216Metric
FB1: MPZ2012S601AT000; C_0805_2012Metric
FB2: 0R; C_0805_2012Metric
FID1, FID2, FID3: Fiducial_1mm_Mask2mm
H1, H2, H3: MountingHole_3.2mm_M3_Pad_Via
J1: TO-HUB; RJ45_FTP_Shielded_Horizontal
J3: 12V-2x6 IN; CEC_12V2x6_Horizontal
J4: 12V-2x6 OUT pigtail; CEC_12V2x6_Horizontal
J5: USB-C 2.0; USB_C_Receptacle_XKB_U262-16XN-4BVC11
LOGO1: CEC_Logo_Copper
R1: 2.2kΩ; R_0402_1005Metric
R2, R6, R20, R21, R27: 10kΩ; R_0402_1005Metric
R5: 47kΩ; R_0402_1005Metric
R7, R25, R28: 100kΩ; R_0402_1005Metric
R8, R9: 5.1kΩ; R_0402_1005Metric
R10, R11, R12, R13: 1kΩ; R_0402_1005Metric
R26: 43.2kΩ; R_0402_1005Metric
R29: 33kΩ; R_0402_1005Metric
RFH1, RFH2, RFH3, RFH4, RFH5, RFH6: 10Ω; R_0402_1005Metric
RFL1, RFL2, RFL3, RFL4, RFL5, RFL6: 10Ω; R_0402_1005Metric
RS1, RS2, RS3, RS4, RS5, RS6: 1mΩ; R_2512_6332Metric
SW1: BOOT; TS-1088-AR02016
SW2: RESET; TS-1088-AR02016
TH1, TH2: NTC 10k; NTC_0402_1005Metric
U1: ESP32-S3-MINI-1-N4R2; ESP32-S2-MINI-1_NoAntKeepout
U2: TJA1051T/3; SOIC-8_3.9x4.9mm_P1.27mm
U3: LP5907MFX-3.3; SOT-23-5
U4: REF3030; REF3030_DBZ3
U5: TPS2121RUXR; RUX0012A
U10, U11, U12, U13, U14, U15: INA240A3; SOIC-8_3.9x4.9mm_P1.27mm

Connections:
+3V3: C2.1, C3.1, C7.1, C8.1, C10.1, C11.1, C12.1, C13.1, C14.1, C15.1, C23.1, R2.1, TH1.1, TH2.1, U1.3 (3V3), U2.5 (VIO), U3.5 (OUT), U4.1 (IN), U10.6 (V+), U11.6 (V+), U12.6 (V+), U13.6 (V+), U14.6 (V+), U15.6 (V+)
+5VSB: C1.1, C4.1, C6.1, J1.1 (VCC), U2.3 (VCC), U3.1 (IN), U3.3 (EN), U5.1, U5.8
/08-usb/U5_ILM: R25.1, U5.10
/08-usb/U5_OV1: R26.2, R27.1, U5.5
/08-usb/U5_PR1: R28.2, R29.1, U5.6
/08-usb/U5_SS: C26.1, U5.11
/08-usb/VBUS_F: F1.2, FB1.1
/CAN_H: J1.3 (CAN1_H), U2.7 (CANH)
/CAN_L: J1.6 (CAN1_L), U2.6 (CANL)
/CAN_RX: U1.22 (IO18), U2.4 (RXD)
/CAN_TX: U1.21 (IO17), U2.1 (TXD)
/DETECT: D1.1 (K), J1.8 (DETECT), R1.1, R7.1
/DETECT_SENSE: R7.2, U1.14 (IO10)
/EN: C5.1, R2.2, SW2.2, U1.45 (EN)
/GPIO0: SW1.2, U1.4 (IO0)
/IN1_N: CF1.2, RFL1.2, U10.1 (-)
/IN1_P: CF1.1, RFH1.2, U10.8 (+)
/IN2_N: CF2.2, RFL2.2, U11.1 (-)
/IN2_P: CF2.1, RFH2.2, U11.8 (+)
/IN3_N: CF3.2, RFL3.2, U12.1 (-)
/IN3_P: CF3.1, RFH3.2, U12.8 (+)
/IN4_N: CF4.2, RFL4.2, U13.1 (-)
/IN4_P: CF4.1, RFH4.2, U13.8 (+)
/IN5_N: CF5.2, RFL5.2, U14.1 (-)
/IN5_P: CF5.1, RFH5.2, U14.8 (+)
/IN6_N: CF6.2, RFL6.2, U15.1 (-)
/IN6_P: CF6.1, RFH6.2, U15.8 (+)
/ISENSEP1: U1.5 (IO1), U10.5
/ISENSEP2: U1.6 (IO2), U11.5
/ISENSEP3: U1.7 (IO3), U12.5
/ISENSEP4: U1.8 (IO4), U13.5
/ISENSEP5: U1.9 (IO5), U14.5
/ISENSEP6: U1.10 (IO6), U15.5
/SB_CBL_PRES: J3.16 (SENSE), J4.16 (SENSE), R13.1
/SB_CBL_PRES_GPIO: R13.2, U1.16 (IO12)
/SB_PWR_STABLE: J3.15 (SENSE), J4.15 (SENSE), R12.1
/SB_PWR_STABLE_GPIO: R12.2, U1.15 (IO11)
/SB_SENSE0: J3.13 (SENSE), J4.13 (SENSE), R10.1
/SB_SENSE0_GPIO: R10.2, U1.19 (IO15)
/SB_SENSE1: J3.14 (SENSE), J4.14 (SENSE), R11.1
/SB_SENSE1_GPIO: R11.2, U1.13 (IO9)
/SENSEP1_HI: J3.1 (+12V), RFH1.1, RS1.1
/SENSEP1_LO: J4.6 (+12V), RFL1.1, RS1.2
/SENSEP2_HI: J3.2 (+12V), RFH2.1, RS2.1
/SENSEP2_LO: J4.5 (+12V), RFL2.1, RS2.2
/SENSEP3_HI: J3.3 (+12V), RFH3.1, RS3.1
/SENSEP3_LO: J4.4 (+12V), RFL3.1, RS3.2
/SENSEP4_HI: J3.4 (+12V), RFH4.1, RS4.1
/SENSEP4_LO: J4.3 (+12V), RFL4.1, RS4.2
/SENSEP5_HI: J3.5 (+12V), RFH5.1, RS5.1
/SENSEP5_LO: J4.2 (+12V), RFL5.1, RS5.2
/SENSEP6_HI: J3.6 (+12V), R5.1, RFH6.1, RS6.1
/SENSEP6_LO: J4.1 (+12V), RFL6.1, RS6.2
/TEMP1: C20.1, R20.1, TH1.2, U1.17 (IO13)
/TEMP2: C21.1, R21.1, TH2.2, U1.18 (IO14)
/USB_CC1: J5.A5 (CC1), R8.1
/USB_CC2: J5.B5 (CC2), R9.1
/USB_DM: D3.3, D3.4, J5.A7 (D-), J5.B7 (D-), U1.23 (USB_D-)
/USB_DP: D3.1, D3.6, J5.A6 (D+), J5.B6 (D+), U1.24 (USB_D+)
/VBUS: C9.1, C27.1, C28.1, FB1.2, U5.2
/VBUS_RAW: D3.5, D4.1, F1.1, J5.A4 (VBUS), J5.A9 (VBUS), J5.B4 (VBUS), J5.B9 (VBUS)
/VRAIL_DIV: C24.1, R5.2, R6.1, U1.11 (IO7)
/VREF: C22.1, U1.12 (IO8), U4.2 (OUT)
GND: C1.2, C2.2, C3.2, C4.2, C5.2, C6.2, C7.2, C8.2, C9.2, C10.2, C11.2, C12.2, C13.2, C14.2, C15.2, C20.2, C21.2, C22.2, C23.2, C24.2, C26.2, C27.2, C28.2, D1.2 (A), D3.2, D4.2, H1.1, H2.1, H3.1, J1.2 (GND), J1.SH1 (SHIELD), J1.SH2 (SHIELD), J3.7 (GND), J3.8 (GND), J3.9 (GND), J3.10 (GND), J3.11 (GND), J3.12 (GND), J4.7 (GND), J4.8 (GND), J4.9 (GND), J4.10 (GND), J4.11 (GND), J4.12 (GND), J5.A1 (GND), J5.A12 (GND), J5.B1 (GND), J5.B12 (GND), J5.S1 (SHIELD), R1.2, R6.2, R8.2, R9.2, R20.2, R21.2, R25.2, R27.2, R29.2, SW1.1, SW2.1, U1.1 (GND), U1.2 (GND), U1.42 (GND), U1.43 (GND), U1.46 (GND), U1.47 (GND), U1.48 (GND), U1.49 (GND), U1.50 (GND), U1.51 (GND), U1.52 (GND), U1.53 (GND), U1.54 (GND), U1.55 (GND), U1.56 (GND), U1.57 (GND), U1.58 (GND), U1.59 (GND), U1.60 (GND), U1.61 (GND), U1.62 (GND), U1.63 (GND), U1.64 (GND), U1.65 (GND), U2.2 (GND), U2.8 (S), U3.2 (GND), U4.3 (GND), U5.3, U5.4, U5.12, U10.2 (GND), U10.3 (REF2), U10.4 (GND), U10.7 (REF1), U11.2 (GND), U11.3 (REF2), U11.4 (GND), U11.7 (REF1), U12.2 (GND), U12.3 (REF2), U12.4 (GND), U12.7 (REF1), U13.2 (GND), U13.3 (REF2), U13.4 (GND), U13.7 (REF1), U14.2 (GND), U14.3 (REF2), U14.4 (GND), U14.7 (REF1), U15.2 (GND), U15.3 (REF2), U15.4 (GND), U15.7 (REF1)
VCC_RJ45: FB2.1, R26.1, R28.1, U5.7

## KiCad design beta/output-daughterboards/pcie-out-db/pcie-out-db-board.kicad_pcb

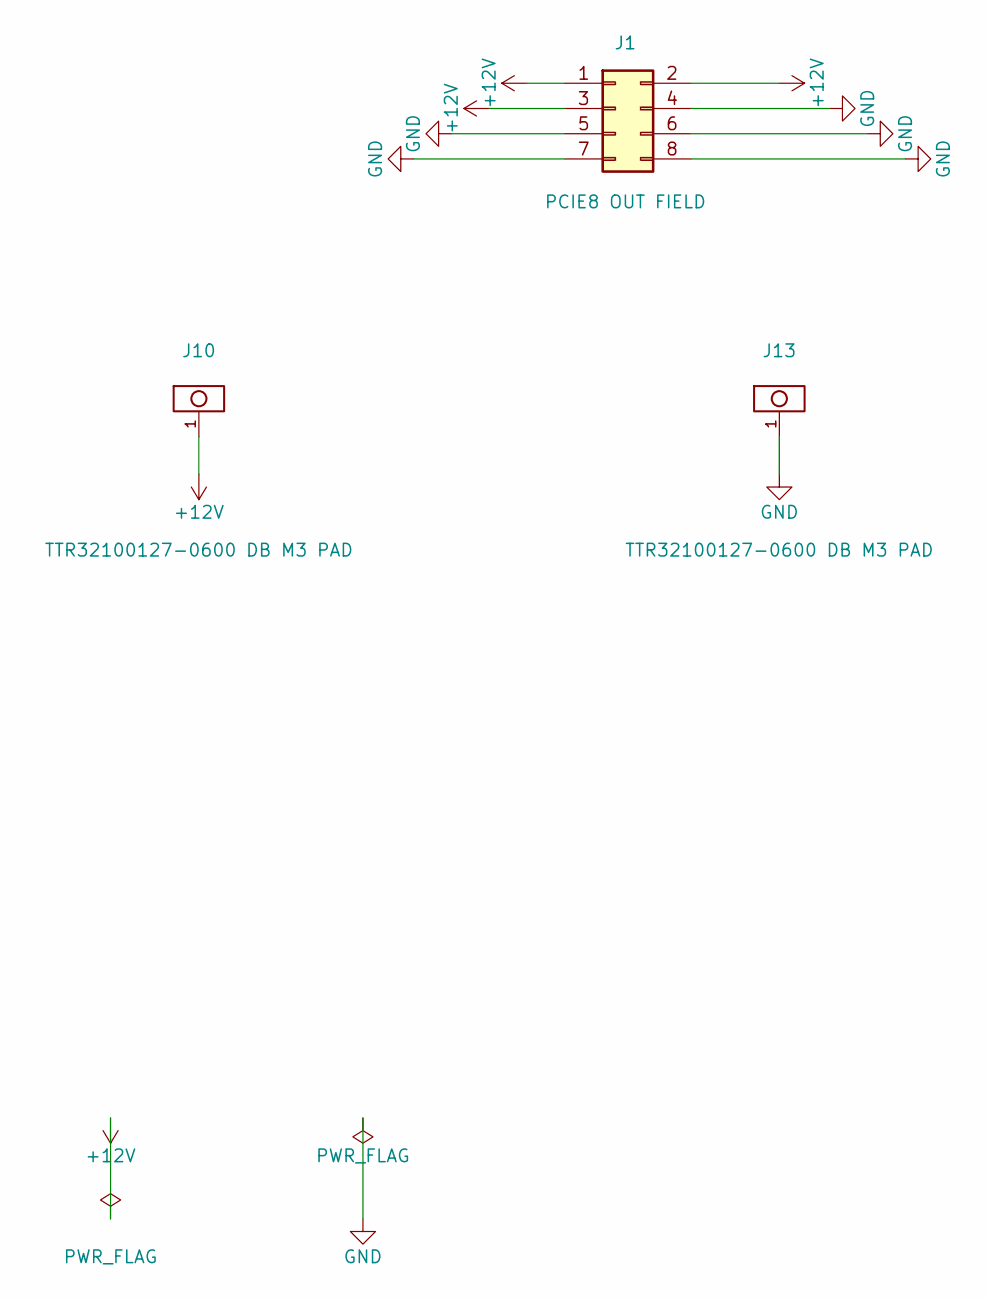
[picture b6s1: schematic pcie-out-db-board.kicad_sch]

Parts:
J1: PCIE8 OUT FIELD; PCIe8_Daughterboard_Field_P4.20mm
J10, J13: TTR32100127-0600 DB M3 PAD; XFCN_TTR32100127-0600_Daughterboard_BoltPad_M3_PROVISIONAL

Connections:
+12V: J1.1, J1.2, J1.3, J10.1
GND: J1.4, J1.5, J1.6, J1.7, J1.8, J13.1

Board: 4 copper layers, 3 parts (0 on the bottom side), 2 nets, no tracks yet.
